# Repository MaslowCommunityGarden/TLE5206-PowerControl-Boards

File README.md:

# TLE5206 PowerControl Boards

PowerControl board based on the TLE5206. Thru-hole and SMD versions

# About the boards:

The standard Maslow PowerControl board uses a pair of simple surface-mount motor-control chips, the L298P013TR, to control the motors. Each chip can control two motors, up to total 4A divided between the motors. Only three motors are provisioned in the release version of the board. There has been concern about the current capacity of these chips and there have been instances where the chips have been damaged when software malfunctioned. Once a chip is damaged, the board would require replacing a 20-pin surface-mount chip to repair.

The TLE5206 offers higher current capacity, over-temperature and over-current detection and protection, along with a simpler package. In addition, there is a thru-hole version of the chip available that would allow a thru-hole version of the board, easier for some users to construct or repair. While the control pins are different from the L298 chips, the firmware requires very little change to work with the TLE5206.

This is a first stab at using the TLE5206 chips on the PowerControl board.
 -  The Electronics folder has EagleCAD board and schematic files for a SMD version and a thru-hole version. I've built and tested both.
 -  The Firmware has been merged with the main MaslowCNC Firmware branch. It adds three true PWM pins to the AUX group which might be used for spindle control with some software development. It doesn't implement the software over-current detection that the TLE5206 offers. For now, the chips sense the over-current or over-temperature condition and protect themselves by turning off the outputs. Use the Arduino IDE to upload the master firmware to control the TLE5206 board.

This design brings:
- separate controller chip for each motor
- higher current capacity (5A) per motor
- thru-hole version to aid hand assembly and repair
- board-mounted heat sinks for the thru-hole version
- mounting holes to match three of the Arduino mounting holes
- AUX pins moved to extended end of board
- 4 digital AUX pins
- 2 analog/digital AUX pins
- 3 PWM-capable digital AUX pins
- board version ID pins avoids using SPI pins

It doesn't bring:
- additional motor control channels
- software over-current or over-temperature sensing

# PCBs
======================

Layout

Schematic - SMD version

Schematic - Thruhole version

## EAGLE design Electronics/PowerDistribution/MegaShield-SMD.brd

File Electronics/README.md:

Maslow PCBs
======================

The TLE5206 offers over-temperature and over-current detection and protection.

This design brings:
- separate controller chip for each motor
- higher current capacity (5A) per motor
- thru-hole parts to aid hand assembly and repair
- board-mounted heat sinks for the thru-hole version
- mounting holes to match the Arduino Mega2560
- AUX pins on extended end of board
- 4 digital AUX pins
- 2 analog/digital AUX pins
- 3 PWM-capable AUX pins
- board version ID pins avoids using SPI pins

Layout
  - thru-hole

  - SMD

Schematic
- thru-hole

- SMD

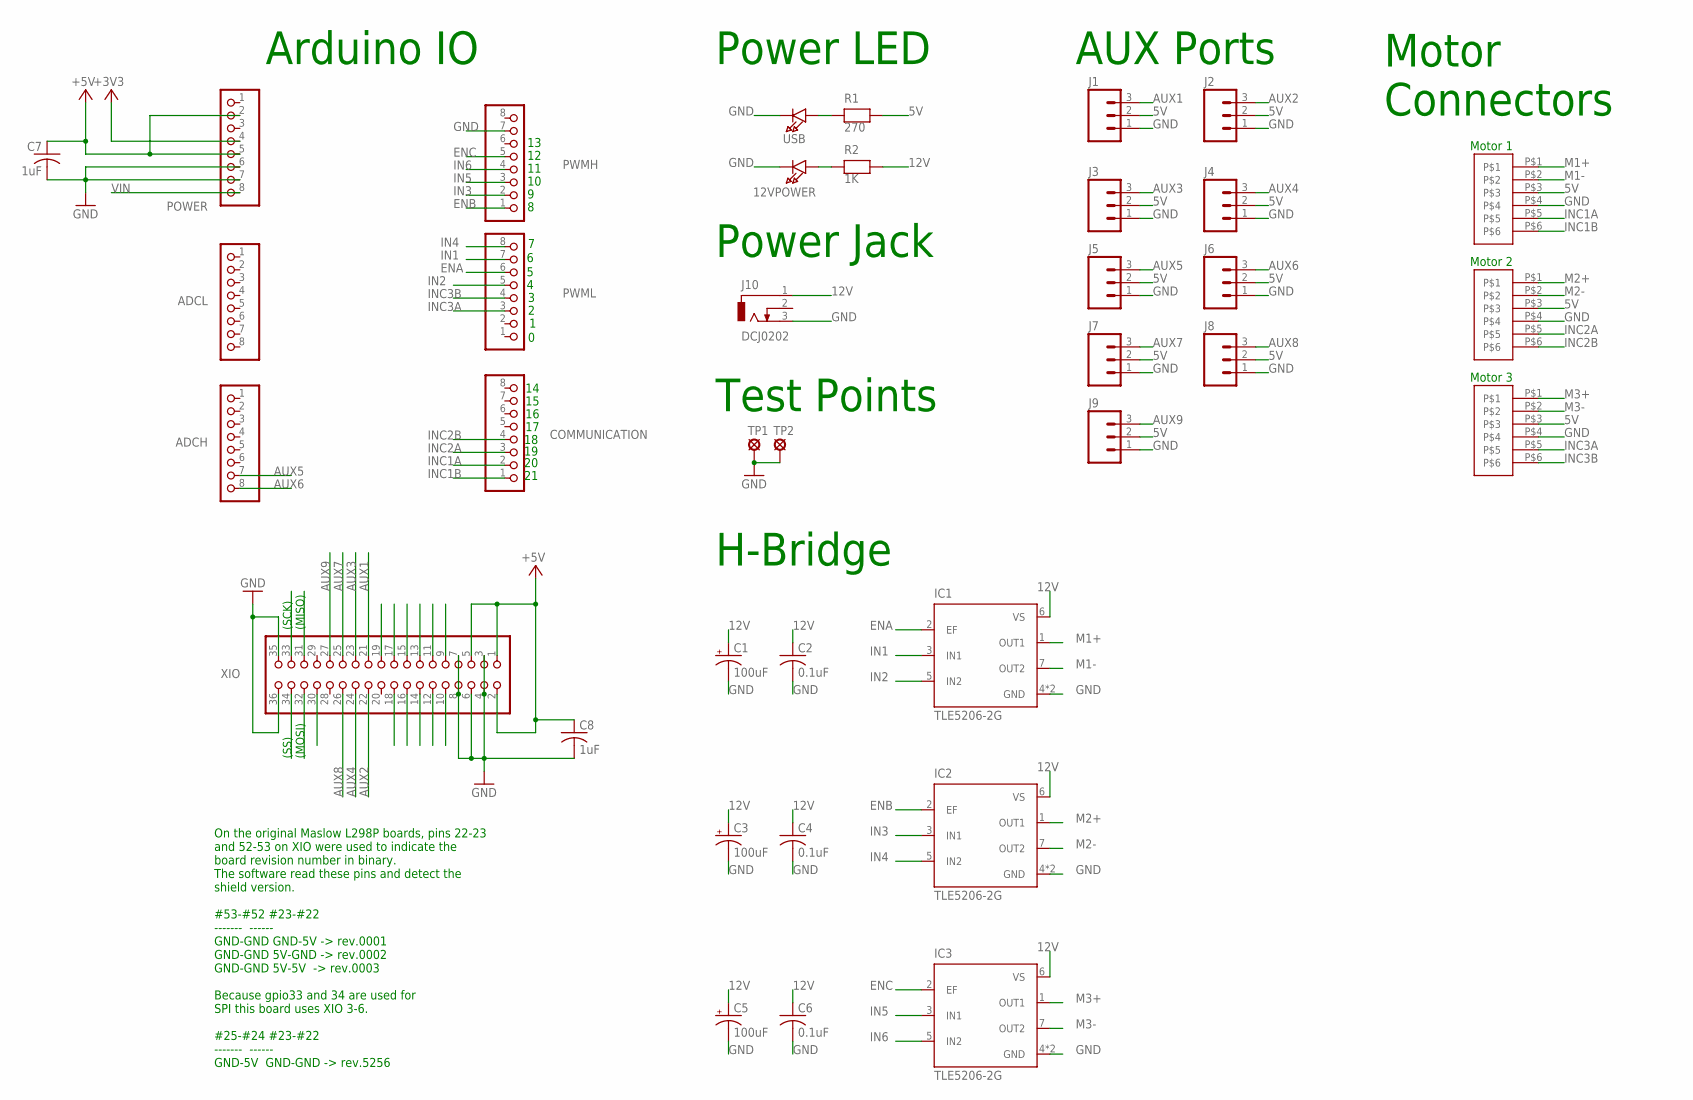
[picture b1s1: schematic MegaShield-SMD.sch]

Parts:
12VPOWER: LED1206; CHIPLED_1206
ADCH: 8x1F-H8.5; 1X08
ADCL: PINHD-1X8; 1X08
C1, C3, C5: 100uF; PANASONIC_E
C2, C4, C6: 0.1uF; C0805K
C7, C8: 1uF; C0805K
COMMUNICATION: PINHD-1X8; 1X08
IC1, IC2: TLE5206-2G; INF-PG-TO263-7-1_L_1PRIMARY
IC3: TLE5206-2G; INF-PG-TO263-7-1_L_1PRIMARY; DIGIKEY TLE5206-2S-ND
J1, J2, J3, J4, J5, J6, J7, J8, J9: M03LOCK; 1X03_LOCK
J10: DCJ0202
MP1, MP2, MP3: JST-PH-6; JST-PHR-6-SMD
POWER: 8x1F-H8.5; 1X08
PWMH: PINHD-1X8; 1X08
PWML: PINHD-1X8; 1X08
R1: 270; 0805
R2: 1K; 0805
TP1, TP2: LSP10
USB: LED1206; CHIPLED_1206
XIO: 18x2F-H8.5; 2X18

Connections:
5V: C7.1, C8.1, J1.2, J2.2, J3.2, J4.2, J5.2, J6.2, J7.2, J8.2, J9.2, MP1.P$3, MP2.P$3, MP3.P$3, POWER.2, POWER.5, R1.2, XIO.1, XIO.2, XIO.5
12V: C1.+, C2.1, C3.+, C4.1, C5.+, C6.1, IC1.6 (VS), IC2.6 (VS), IC3.6 (VS), J10.1, R2.2
+3V3: POWER.4
AUX1: J1.3, XIO.21
AUX2: J2.3, XIO.22
AUX3: J3.3, XIO.23
AUX4: J4.3, XIO.24
AUX5: ADCH.7, J5.3
AUX6: ADCH.8, J6.3
AUX7: J7.3, XIO.25
AUX8: J8.3, XIO.26
AUX9: J9.3, XIO.27
ENA: IC1.2 (EF), PWML.6
ENB: IC2.2 (EF), PWMH.1
ENC: IC3.2 (EF), PWMH.5
GND: 12VPOWER.C, C1.-, C2.2, C3.-, C4.2, C5.-, C6.2, C7.2, C8.2, IC1.4 (GND), IC1.8 (GND), IC2.4 (GND), IC2.8 (GND), IC3.4 (GND), IC3.8 (GND), J1.1, J2.1, J3.1, J4.1, J5.1, J6.1, J7.1, J8.1, J9.1, J10.3, MP1.P$4, MP2.P$4, MP3.P$4, POWER.6, POWER.7, PWMH.7, TP1.MP, TP2.MP, USB.C, XIO.3, XIO.4, XIO.6, XIO.7, XIO.8, XIO.35, XIO.36
IN1: IC1.3 (IN1), PWML.7
IN2: IC1.5 (IN2), PWML.5
IN3: IC2.3 (IN1), PWMH.2
IN4: IC2.5 (IN2), PWML.8
IN5: IC3.3 (IN1), PWMH.3
IN6: IC3.5 (IN2), PWMH.4
INC1A: COMMUNICATION.2, MP1.P$5
INC1B: COMMUNICATION.1, MP1.P$6
INC2A: COMMUNICATION.3, MP2.P$5
INC2B: COMMUNICATION.4, MP2.P$6
INC3A: MP3.P$5, PWML.3
INC3B: MP3.P$6, PWML.4
M1+: IC1.1 (OUT1), MP1.P$1
M1-: IC1.7 (OUT2), MP1.P$2
M2+: IC2.1 (OUT1), MP2.P$1
M2-: IC2.7 (OUT2), MP2.P$2
M3+: IC3.1 (OUT1), MP3.P$1
M3-: IC3.7 (OUT2), MP3.P$2
unnamed: R1.1, USB.A
unnamed: 12VPOWER.A, R2.1
PA6: XIO.9
PA7: XIO.10
PB0: XIO.34
PB1: XIO.33
PB2: XIO.32
PB3: XIO.31
PC0: XIO.18
PC1: XIO.17
PC2: XIO.16
PC3: XIO.15
PC4: XIO.14
PC5: XIO.13
PC6: XIO.12
PC7: XIO.11
PD7: XIO.19
PL0: XIO.30
VIN: POWER.8

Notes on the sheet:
Motor 1
Motor 2
H-Bridge
Power LED
Power Jack
Arduino IO
AUX Ports
Motor Connectors
Motor 3
On the original Maslow L298P boards, pins 22-23 and 52-53 on XIO were used to indicate the board revision number in binary. The software read these pins and detect the shield version. #53-#52 #23-#22 ------- ------ GND-GND GND-5V -> rev.0001 GND-GND 5V-GND -> rev.0002 GND-GND 5V-5V -> rev.0003 Beca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
(SS)
(MOSI)
(SCK)
(MISO)
Test Points

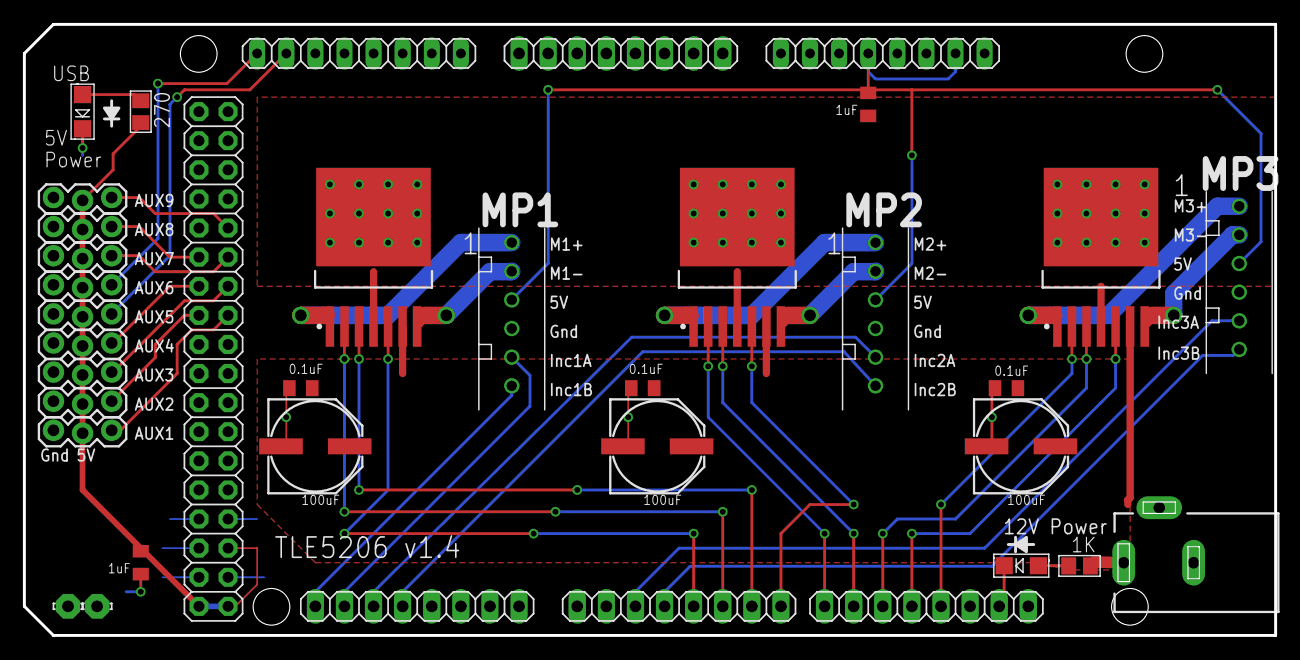
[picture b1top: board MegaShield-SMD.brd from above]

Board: 2 copper layers, 109.2 x 53.3 mm, 37 parts (0 on the bottom side), 35 nets.

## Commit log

2018-04-10 init commit
2018-04-10 Update the project files
2018-04-10 Update README.md
    update firmware version to 1.11
2018-04-10 Add the contents
2018-04-10 Add schematics and layouts to Readme
2018-04-10 Correct schematic links
2018-04-10 Add labels
2018-04-10 replace picture
2018-04-10 add JPGs at root
2018-05-14 Remove Firmware and note merge with master branch.
    PR# 449 merges the TLE5206 code with the main MaslowCNC branch. The separate code is no longer necessary.
2018-06-05 Convert ROBOT.md file to use json format
    Using the json format will make it easier for us to store meta data to categorize and tag projects. The garden is filling up (which is AMAZING!!) but its starting to get a little cluttered. I am hopi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
2018-09-09 Move MP3 to prevent Inc3B from shorting against USB connector of Arduino Mega

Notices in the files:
parts and their libraries:
SparkFun-Connectors: Licensing: Creative Commons ShareAlike 4.0 International - https://creativecommons.org/licenses/by-sa/4.0
SparkFun: Licensing: CC v3.0 Share-Alike You are welcome to use this library for commercial purposes.
